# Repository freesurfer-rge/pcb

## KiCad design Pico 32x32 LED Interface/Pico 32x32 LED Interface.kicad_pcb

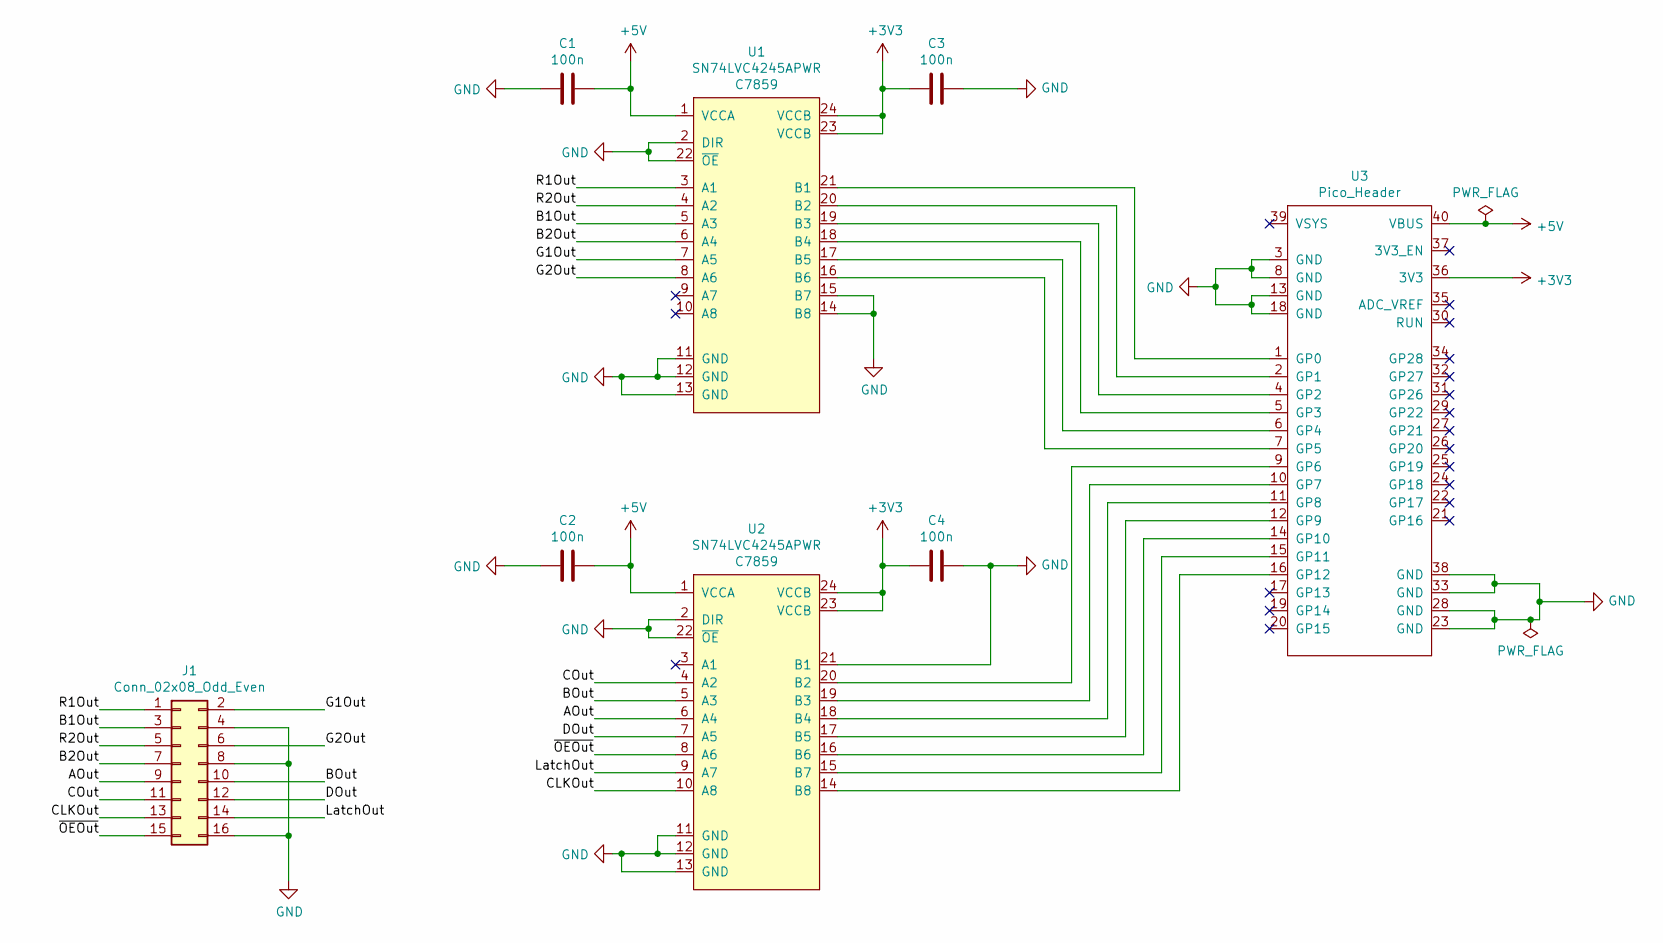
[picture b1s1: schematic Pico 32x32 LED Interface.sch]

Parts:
C1, C3: 100n; C_0402_1005Metric; LCSC C1525
C2, C4: 100n; C_0402_1005Metric_Pad0.74x0.62mm_HandSolder; LCSC C1525
J1: Conn_02x08_Odd_Even; PinHeader_2x08_P2.54mm_Vertical
U1, U2: SN74LVC4245APWR; TSSOP-24_4.4x7.8mm_P0.65mm; LCSC C7859
U3: Pico_Header; Pico_In_Headers

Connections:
+3V3: C3.2, C4.2, U1.23 (VCCB), U1.24 (VCCB), U2.23 (VCCB), U2.24 (VCCB), U3.36 (3V3)
+5V: C1.1, C2.1, U1.1 (VCCA), U2.1 (VCCA), U3.40 (VBUS)
/AOut: J1.9, U2.6 (A4)
/B1Out: J1.3, U1.5 (A3)
/B2Out: J1.7, U1.6 (A4)
/BOut: J1.10, U2.5 (A3)
/CLKOut: J1.13, U2.10 (A8)
/COut: J1.11, U2.4 (A2)
/DOut: J1.12, U2.7 (A5)
/G1Out: J1.2, U1.7 (A5)
/G2Out: J1.6, U1.8 (A6)
/LatchOut: J1.14, U2.9 (A7)
/R1Out: J1.1, U1.3 (A1)
/R2Out: J1.5, U1.4 (A2)
/~OEOut: J1.15, U2.8 (A6)
GND: C1.2, C2.2, C3.1, C4.1, J1.4, J1.8, J1.16, U1.2 (DIR), U1.11 (GND), U1.12 (GND), U1.13 (GND), U1.14 (B8), U1.15 (B7), U1.22 (~OE), U2.2 (DIR), U2.11 (GND), U2.12 (GND), U2.13 (GND), U2.21 (B1), U2.22 (~OE), U3.3 (GND), U3.8 (GND), U3.13 (GND), U3.18 (GND), U3.23 (GND), U3.28 (GND), U3.33 (GND), U3.38 (GND)
unnamed: U1.16 (B6), U3.7 (GP5)
unnamed: U1.17 (B5), U3.6 (GP4)
unnamed: U1.18 (B4), U3.5 (GP3)
unnamed: U1.19 (B3), U3.4 (GP2)
unnamed: U1.20 (B2), U3.2 (GP1)
unnamed: U1.21 (B1), U3.1 (GP0)
unnamed: U2.14 (B8), U3.16 (GP12)
unnamed: U2.15 (B7), U3.15 (GP11)
unnamed: U2.16 (B6), U3.14 (GP10)
unnamed: U2.17 (B5), U3.12 (GP9)
unnamed: U2.18 (B4), U3.11 (GP8)
unnamed: U2.19 (B3), U3.10 (GP7)
unnamed: U2.20 (B2), U3.9 (GP6)

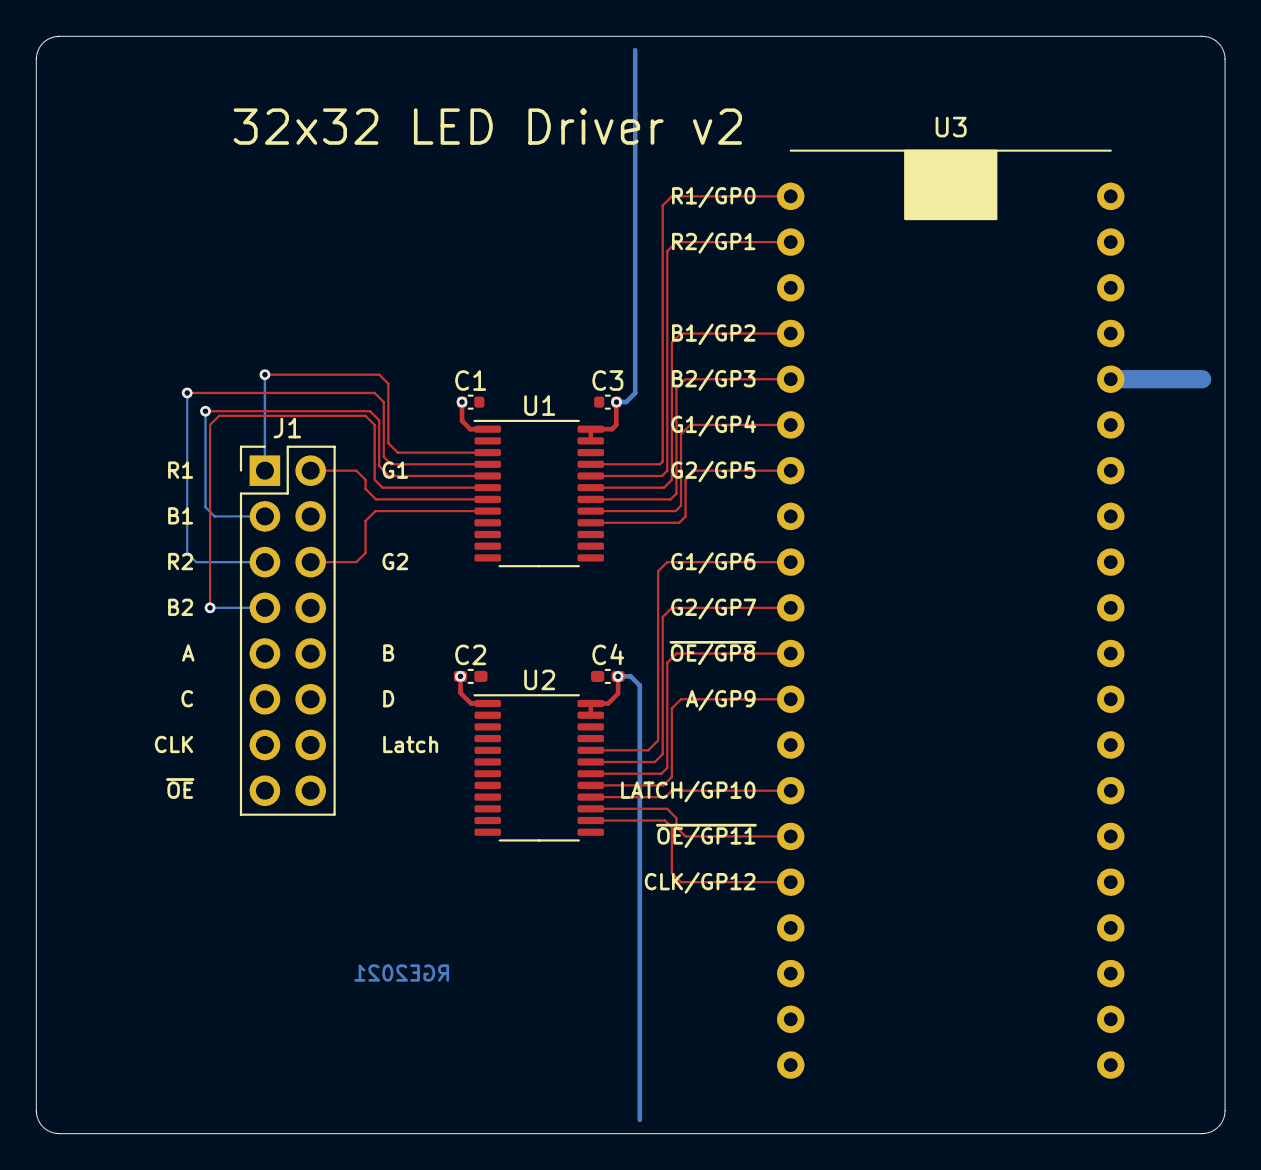
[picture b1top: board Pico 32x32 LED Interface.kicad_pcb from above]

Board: 2 copper layers, 66.0 x 61.0 mm, 8 parts (0 on the bottom side), 29 nets.

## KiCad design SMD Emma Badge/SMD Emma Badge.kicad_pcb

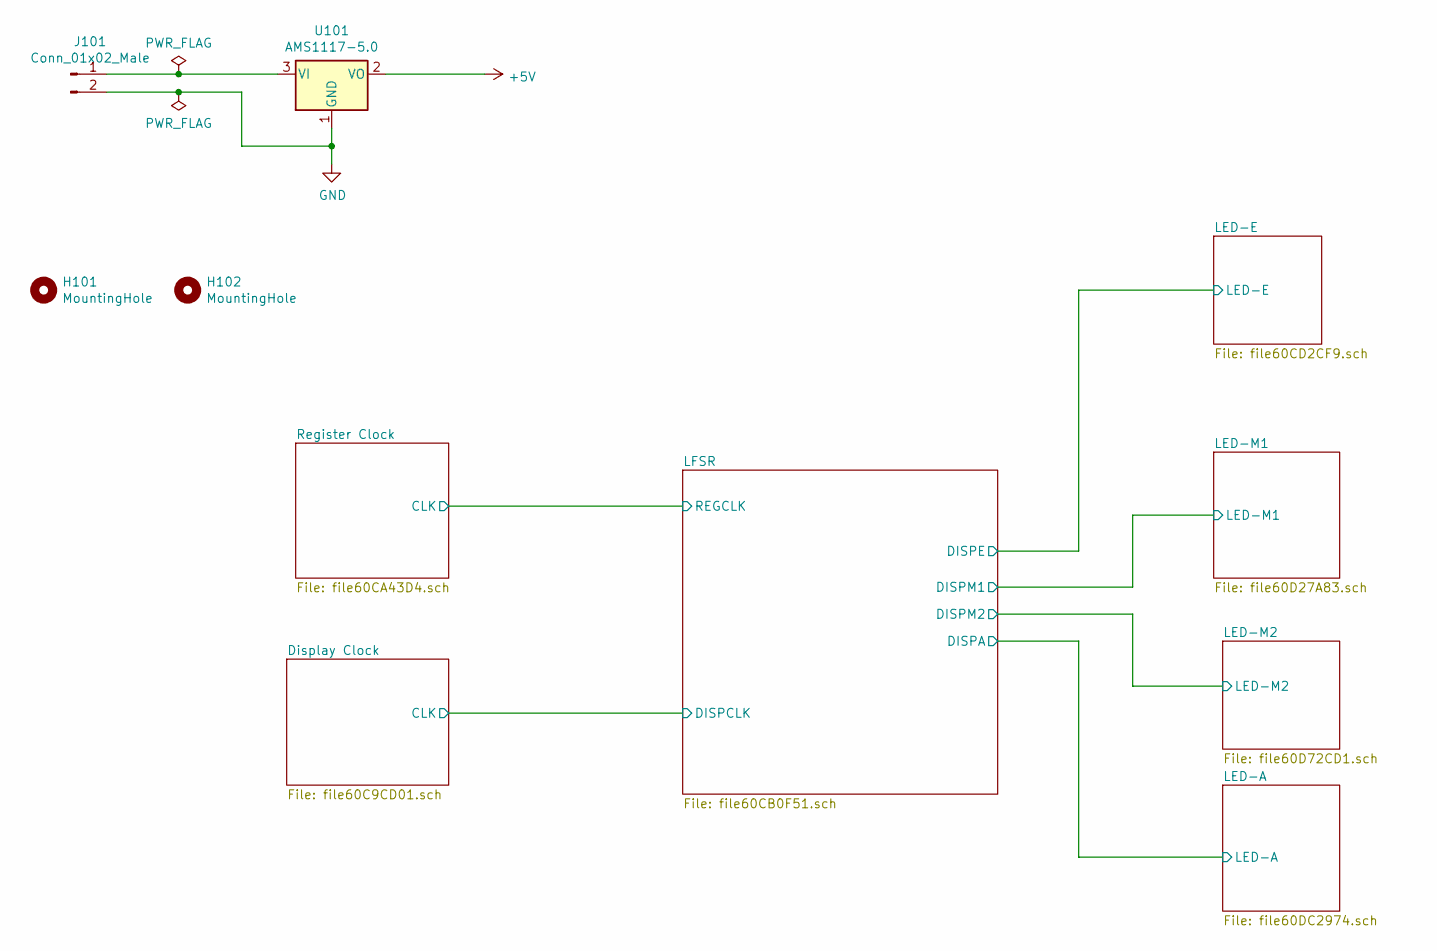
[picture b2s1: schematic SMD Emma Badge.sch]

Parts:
H101, H102: MountingHole; MountingHole_2.5mm
J101: Conn_01x02_Male; PinHeader_1x02_P2.54mm_Vertical
U101: AMS1117-5.0; SOT-223-3_TabPin2; LCSC C6187

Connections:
+5V: U101.2 (VO); also elsewhere on the board
GND: J101.2, U101.1 (GND); also elsewhere on the board
unnamed: J101.1, U101.3 (VI)

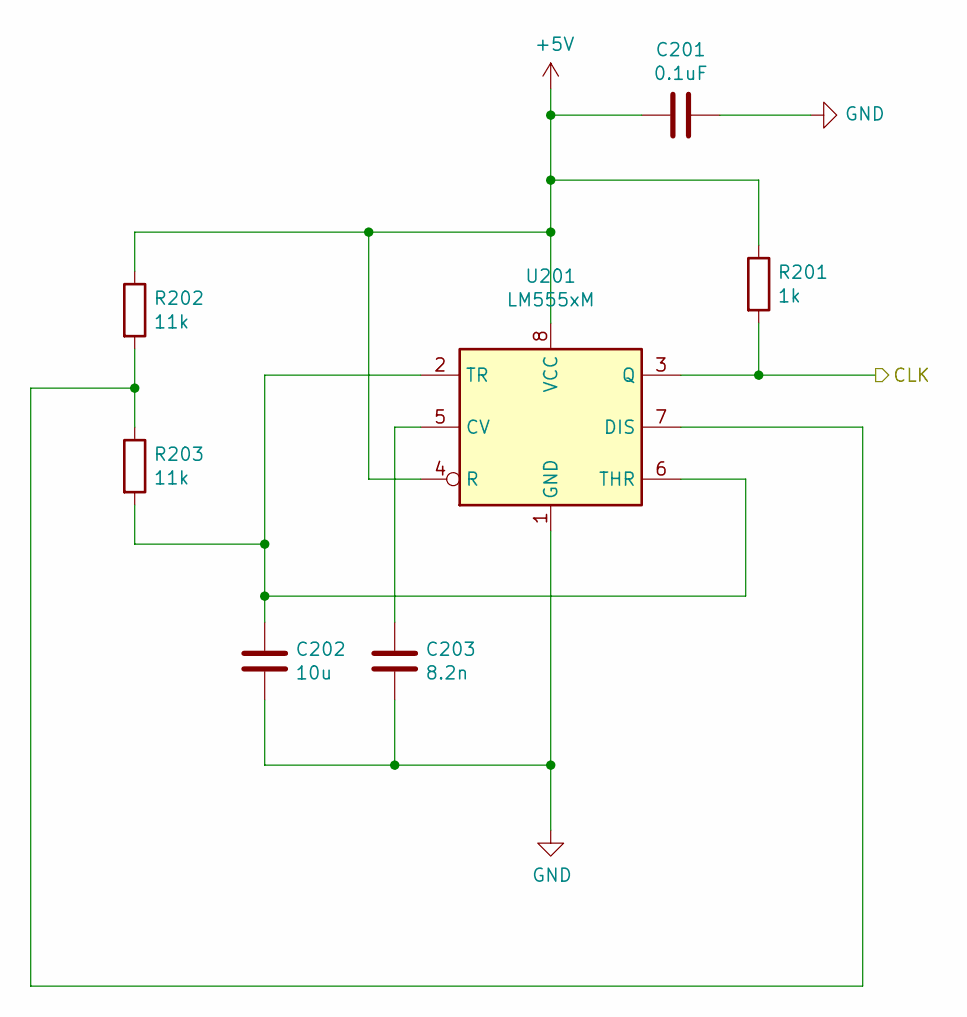
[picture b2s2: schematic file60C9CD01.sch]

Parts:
C201: 0.1uF; C_0603_1608Metric; LCSC C14663
C202: 10u; C_0603_1608Metric; LCSC C19702
C203: 8.2n; C_0603_1608Metric; LCSC C27920
R201: 1k; R_0603_1608Metric; LCSC C21190
R202, R203: 11k; R_0603_1608Metric; LCSC C25950
U201: LM555xM; SOIC-8_3.9x4.9mm_P1.27mm; LCSC C7593

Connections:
+5V: C201.2, R201.1, R202.1, U201.4 (R), U201.8 (VCC); also elsewhere on the board
/Display Clock/CLK: R201.2, U201.3 (Q); also elsewhere on the board
GND: C201.1, C202.2, C203.2, U201.1 (GND); also elsewhere on the board
unnamed: C202.1, R203.2, U201.2 (TR), U201.6 (THR)
unnamed: C203.1, U201.5 (CV)
unnamed: R202.2, R203.1, U201.7 (DIS)

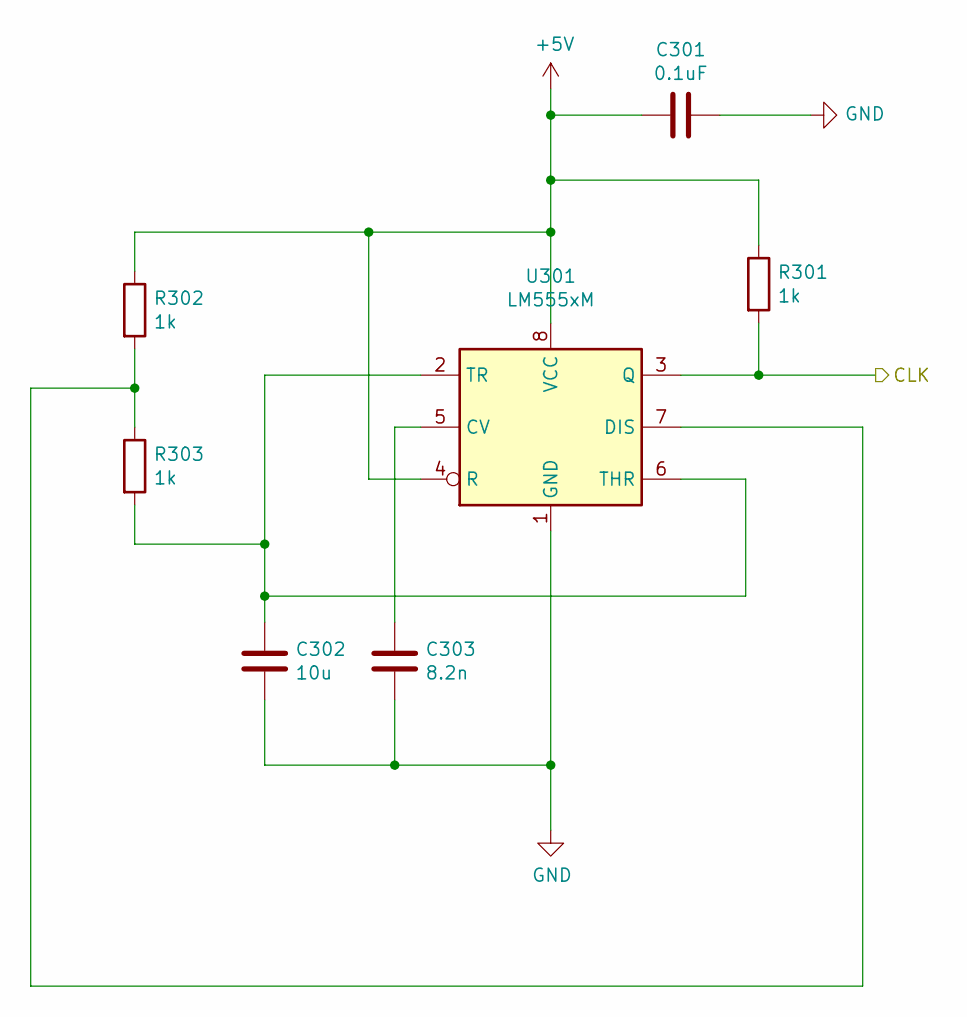
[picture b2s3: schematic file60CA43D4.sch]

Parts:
C301: 0.1uF; C_0603_1608Metric; LCSC C14663
C302: 10u; C_0603_1608Metric; LCSC C19702
C303: 8.2n; C_0603_1608Metric; LCSC C27920
R301, R302, R303: 1k; R_0603_1608Metric; LCSC C21190
U301: LM555xM; SOIC-8_3.9x4.9mm_P1.27mm; LCSC C7593

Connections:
+5V: C301.2, R301.1, R302.1, U301.4 (R), U301.8 (VCC); also elsewhere on the board
/Register Clock/CLK: R301.2, U301.3 (Q); also elsewhere on the board
GND: C301.1, C302.2, C303.2, U301.1 (GND); also elsewhere on the board
unnamed: C302.1, R303.2, U301.2 (TR), U301.6 (THR)
unnamed: C303.1, U301.5 (CV)
unnamed: R302.2, R303.1, U301.7 (DIS)

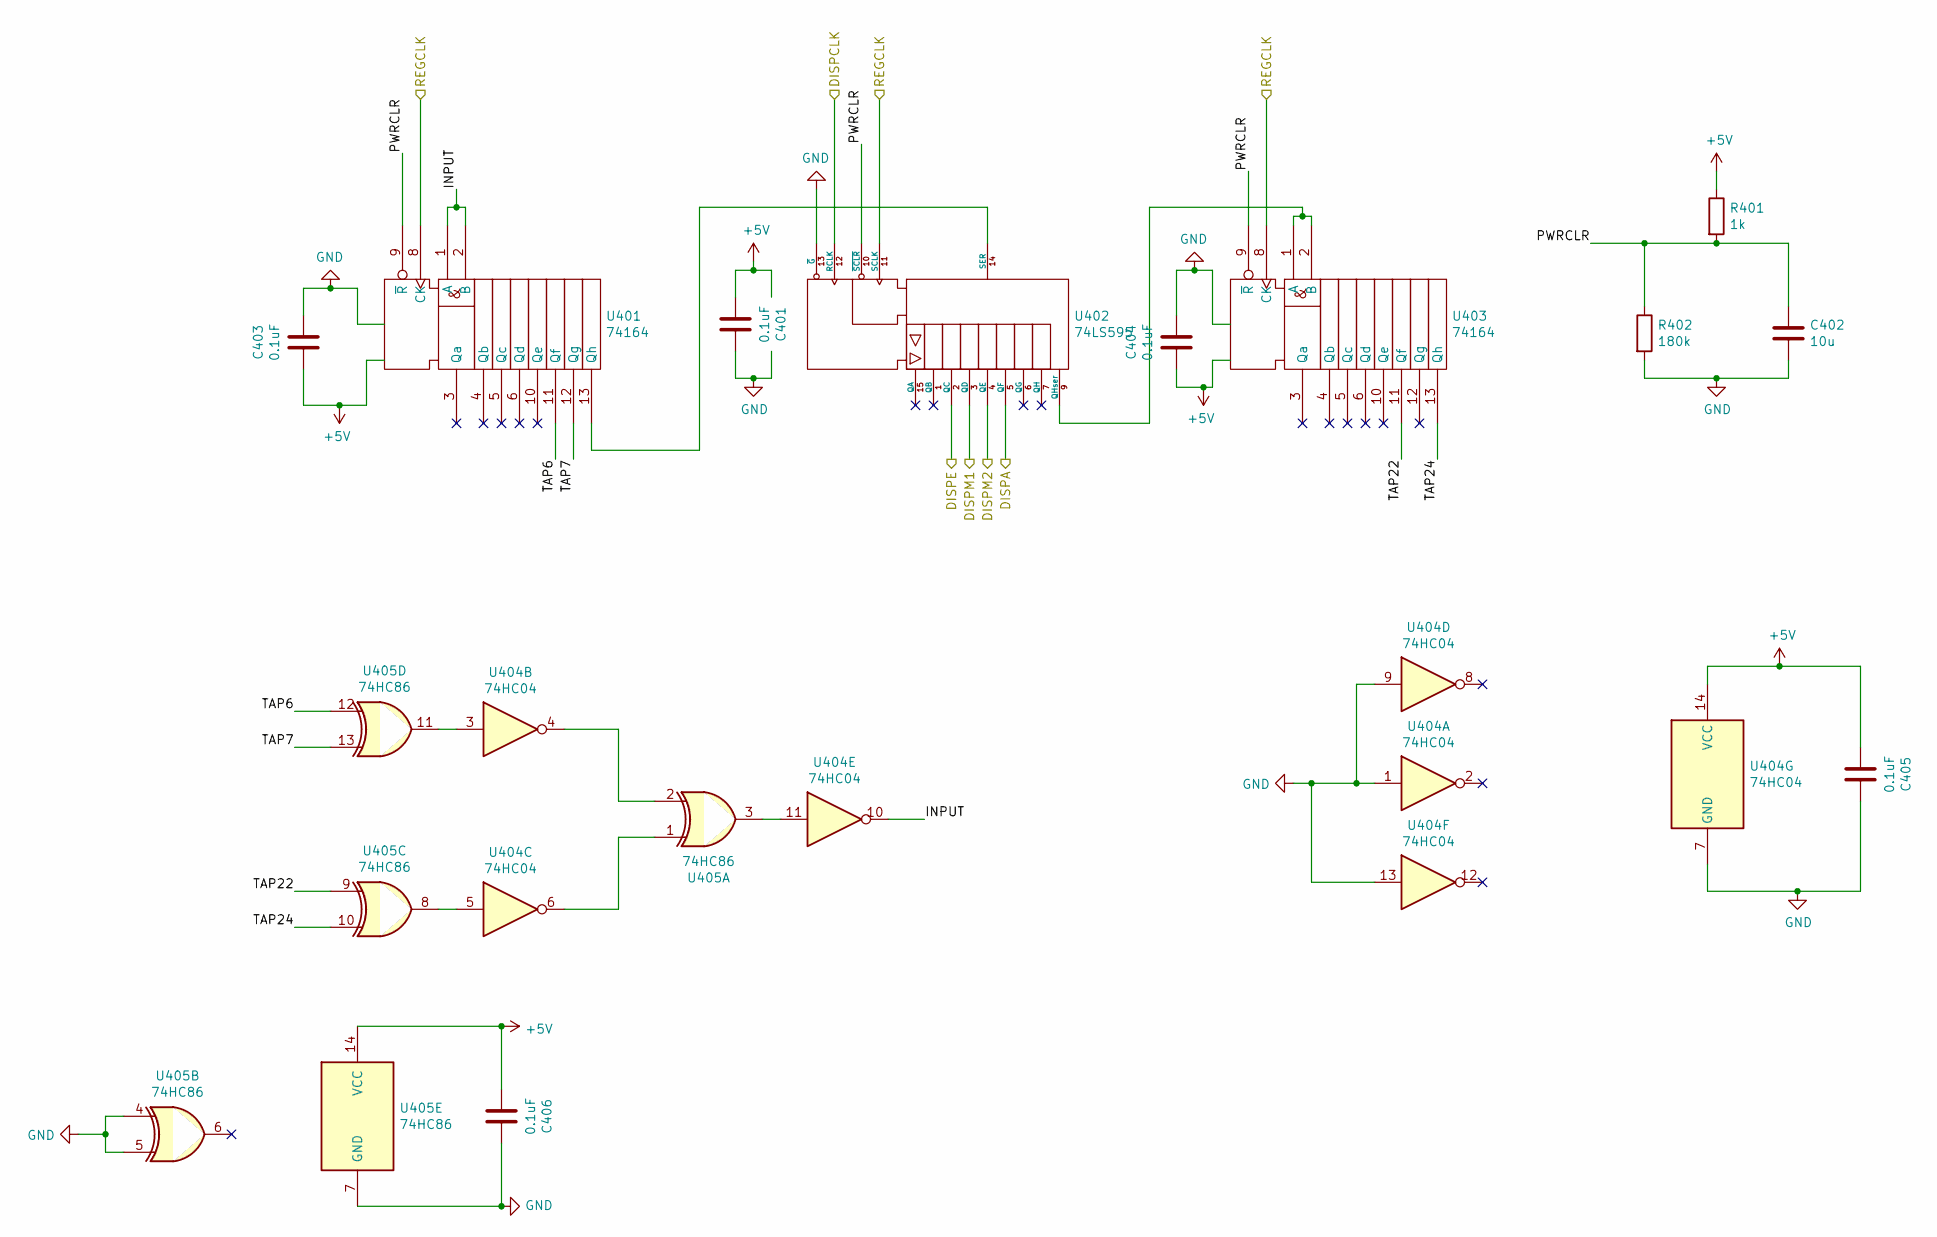
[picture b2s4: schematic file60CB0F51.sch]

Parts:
C401, C403, C404, C405, C406: 0.1uF; C_0603_1608Metric; LCSC C14663
C402: 10u; C_0603_1608Metric; LCSC C19702
R401: 1k; R_0603_1608Metric; LCSC C21190
R402: 180k; R_0603_1608Metric; LCSC C22827
U401, U403: 74164; SOIC-14_3.9x8.7mm_P1.27mm; LCSC C6825
U402: 74LS595; SOIC-16_3.9x9.9mm_P1.27mm; LCSC C5947
U404: 74HC04
U405: 74HC86

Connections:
+5V: C401.2, C403.2, C404.2, C405.2, C406.2, R401.1, U401.14 (Vdd), U402.16 (VCC), U403.14 (Vdd), U404.14 (VCC), U405.14 (VCC); also elsewhere on the board
/Display Clock/CLK: U402.12 (RCLK); also elsewhere on the board
/LFSR/DISPA: U402.5 (QF); also elsewhere on the board
/LFSR/DISPE: U402.2 (QC); also elsewhere on the board
/LFSR/DISPM1: U402.3 (QD); also elsewhere on the board
/LFSR/DISPM2: U402.4 (QE); also elsewhere on the board
/LFSR/INPUT: U401.1 (A), U401.2 (B), U404.10
/LFSR/PWRCLR: C402.1, R401.2, R402.1, U401.9 (~R), U402.10 (~SCLR), U403.9 (~R)
/LFSR/TAP6: U401.11 (Qf), U405.12
/LFSR/TAP7: U401.12 (Qg), U405.13
/LFSR/TAP22: U403.11 (Qf), U405.9
/LFSR/TAP24: U403.13 (Qh), U405.10
/Register Clock/CLK: U401.8 (CK), U402.11 (SCLK), U403.8 (CK); also elsewhere on the board
GND: C401.1, C402.2, C403.1, C404.1, C405.1, C406.1, R402.2, U401.7 (Vss), U402.8 (GND), U402.13 (~G), U403.7 (Vss), U404.1, U404.7 (GND), U404.9, U404.13, U405.4, U405.5, U405.7 (GND); also elsewhere on the board
unnamed: U401.13 (Qh), U402.14 (SER)
unnamed: U402.9 (QHser), U403.1 (A), U403.2 (B)
unnamed: U404.3, U405.11
unnamed: U404.4, U405.2
unnamed: U404.5, U405.8
unnamed: U404.6, U405.1
unnamed: U404.11, U405.3

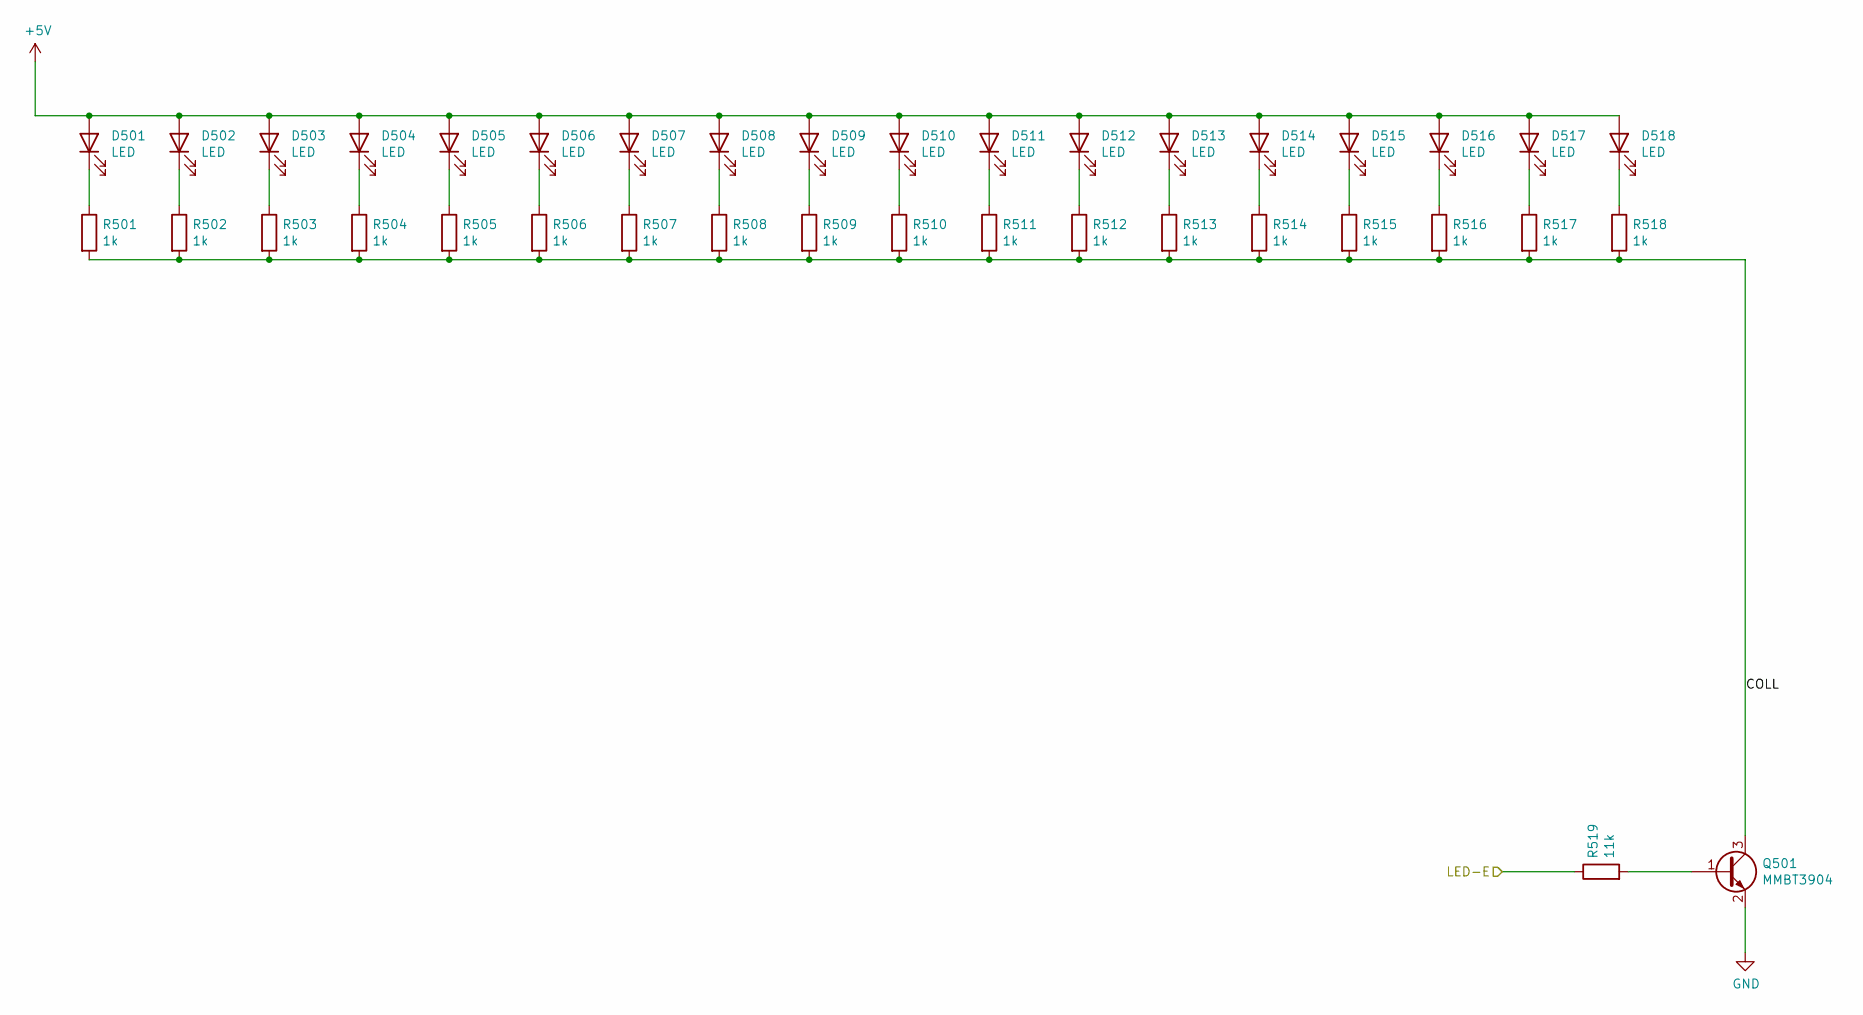
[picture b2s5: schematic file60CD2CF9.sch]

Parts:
D501, D502, D503, D504, D505, D506, D507, D508, D509, D510, D511, D512, D513, D514, D515, D516, D517, D518: LED; LED_0603_1608Metric; LCSC C2286
Q501: MMBT3904; SOT-23; LCSC C20526
R501, R502, R503, R504, R505, R506, R507, R508, R509, R510, R511, R512, R513, R514, R515, R516, R517, R518: 1k; R_0603_1608Metric; LCSC C21190
R519: 11k; R_0603_1608Metric; LCSC C25950

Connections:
+5V: D501.2 (A), D502.2 (A), D503.2 (A), D504.2 (A), D505.2 (A), D506.2 (A), D507.2 (A), D508.2 (A), D509.2 (A), D510.2 (A), D511.2 (A), D512.2 (A), D513.2 (A), D514.2 (A), D515.2 (A), D516.2 (A), D517.2 (A), D518.2 (A); also elsewhere on the board
/LED-E/COLL: Q501.3 (C), R501.2, R502.2, R503.2, R504.2, R505.2, R506.2, R507.2, R508.2, R509.2, R510.2, R511.2, R512.2, R513.2, R514.2, R515.2, R516.2, R517.2, R518.2
/LFSR/DISPE: R519.1; also elsewhere on the board
GND: Q501.2 (E); also elsewhere on the board
unnamed: D501.1 (K), R501.1
unnamed: D502.1 (K), R502.1
unnamed: D503.1 (K), R503.1
unnamed: D504.1 (K), R504.1
unnamed: D505.1 (K), R505.1
unnamed: D506.1 (K), R506.1
unnamed: D507.1 (K), R507.1
unnamed: D508.1 (K), R508.1
unnamed: D509.1 (K), R509.1
unnamed: D510.1 (K), R510.1
unnamed: D511.1 (K), R511.1
unnamed: D512.1 (K), R512.1
unnamed: D513.1 (K), R513.1
unnamed: D514.1 (K), R514.1
unnamed: D515.1 (K), R515.1
unnamed: D516.1 (K), R516.1
unnamed: D517.1 (K), R517.1
unnamed: D518.1 (K), R518.1
unnamed: Q501.1 (B), R519.2

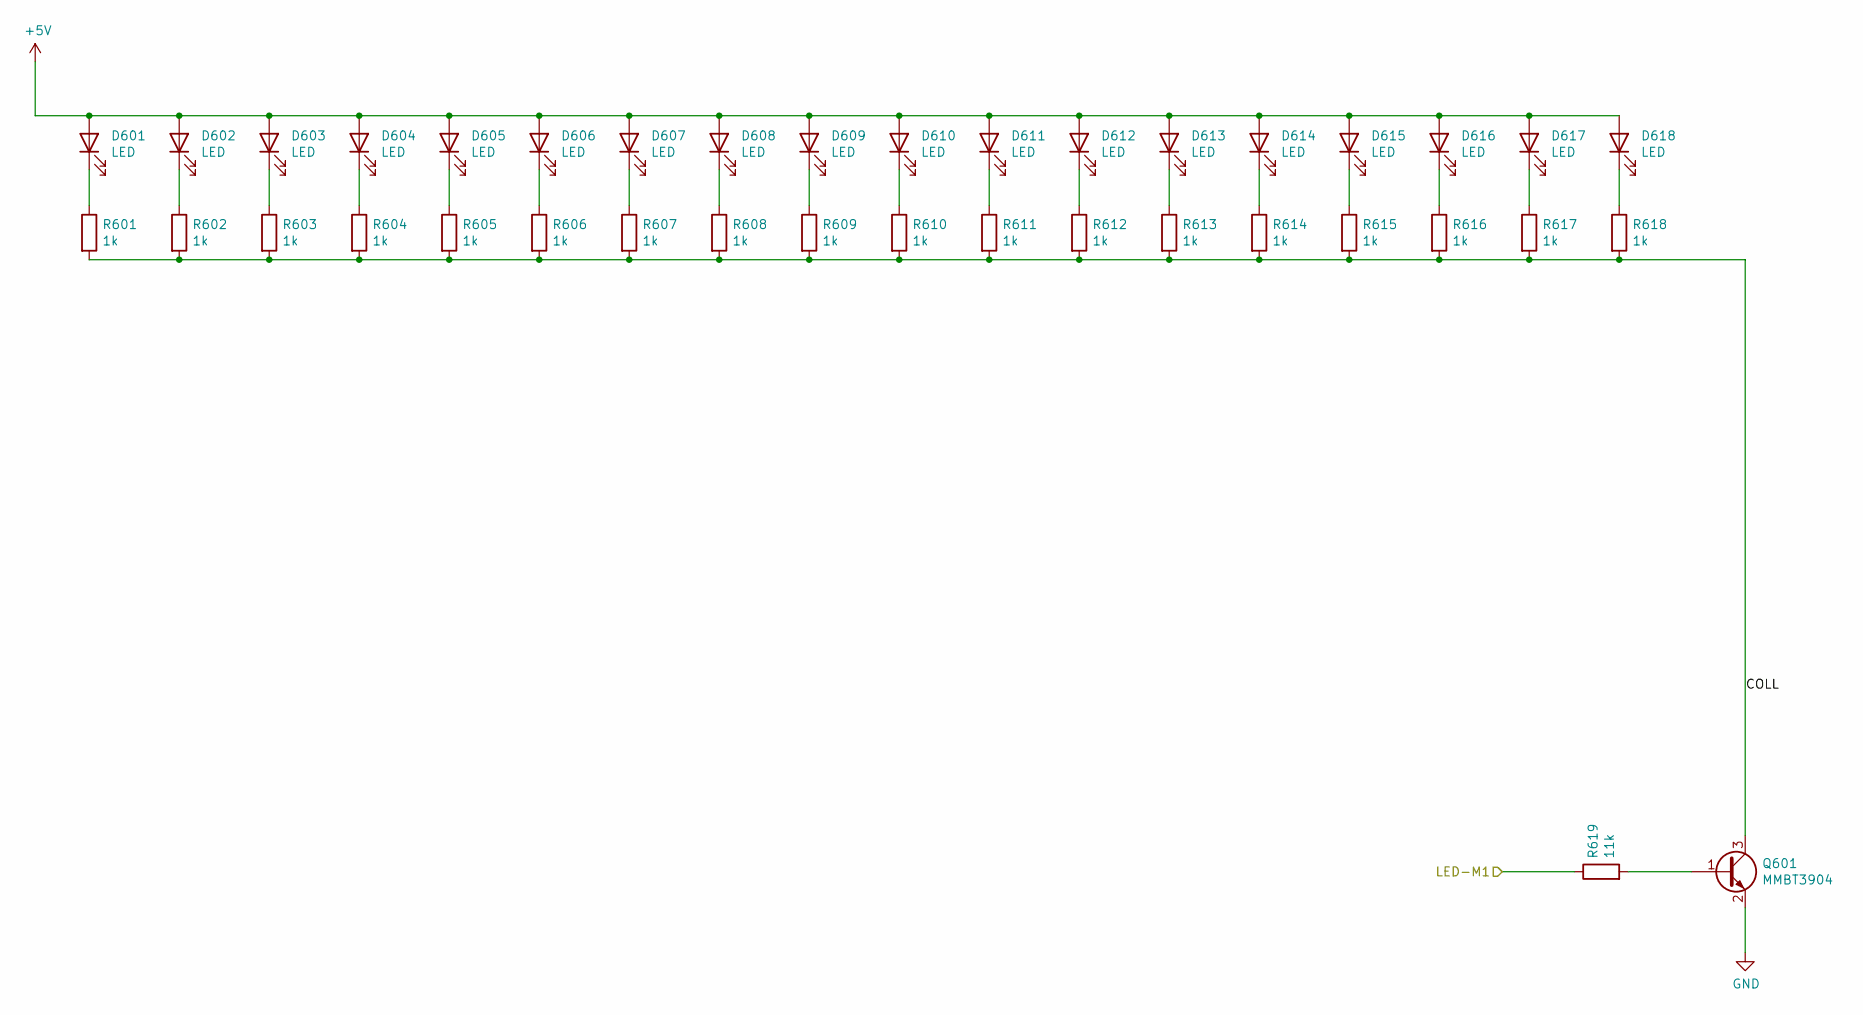
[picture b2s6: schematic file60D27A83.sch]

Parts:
D601, D602, D603, D604, D605, D606, D607, D608, D609, D610, D611, D612, D613, D614, D615, D616, D617, D618: LED; LED_0603_1608Metric; LCSC C2286
Q601: MMBT3904; SOT-23; LCSC C20526
R601, R602, R603, R604, R605, R606, R607, R608, R609, R610, R611, R612, R613, R614, R615, R616, R617, R618: 1k; R_0603_1608Metric; LCSC C21190
R619: 11k; R_0603_1608Metric; LCSC C25950

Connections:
+5V: D601.2 (A), D602.2 (A), D603.2 (A), D604.2 (A), D605.2 (A), D606.2 (A), D607.2 (A), D608.2 (A), D609.2 (A), D610.2 (A), D611.2 (A), D612.2 (A), D613.2 (A), D614.2 (A), D615.2 (A), D616.2 (A), D617.2 (A), D618.2 (A); also elsewhere on the board
/LED-M1/COLL: Q601.3 (C), R601.2, R602.2, R603.2, R604.2, R605.2, R606.2, R607.2, R608.2, R609.2, R610.2, R611.2, R612.2, R613.2, R614.2, R615.2, R616.2, R617.2, R618.2
/LFSR/DISPM1: R619.1; also elsewhere on the board
GND: Q601.2 (E); also elsewhere on the board
unnamed: D601.1 (K), R601.1
unnamed: D602.1 (K), R602.1
unnamed: D603.1 (K), R603.1
unnamed: D604.1 (K), R604.1
unnamed: D605.1 (K), R605.1
unnamed: D606.1 (K), R606.1
unnamed: D607.1 (K), R607.1
unnamed: D608.1 (K), R608.1
unnamed: D609.1 (K), R609.1
unnamed: D610.1 (K), R610.1
unnamed: D611.1 (K), R611.1
unnamed: D612.1 (K), R612.1
unnamed: D613.1 (K), R613.1
unnamed: D614.1 (K), R614.1
unnamed: D615.1 (K), R615.1
unnamed: D616.1 (K), R616.1
unnamed: D617.1 (K), R617.1
unnamed: D618.1 (K), R618.1
unnamed: Q601.1 (B), R619.2

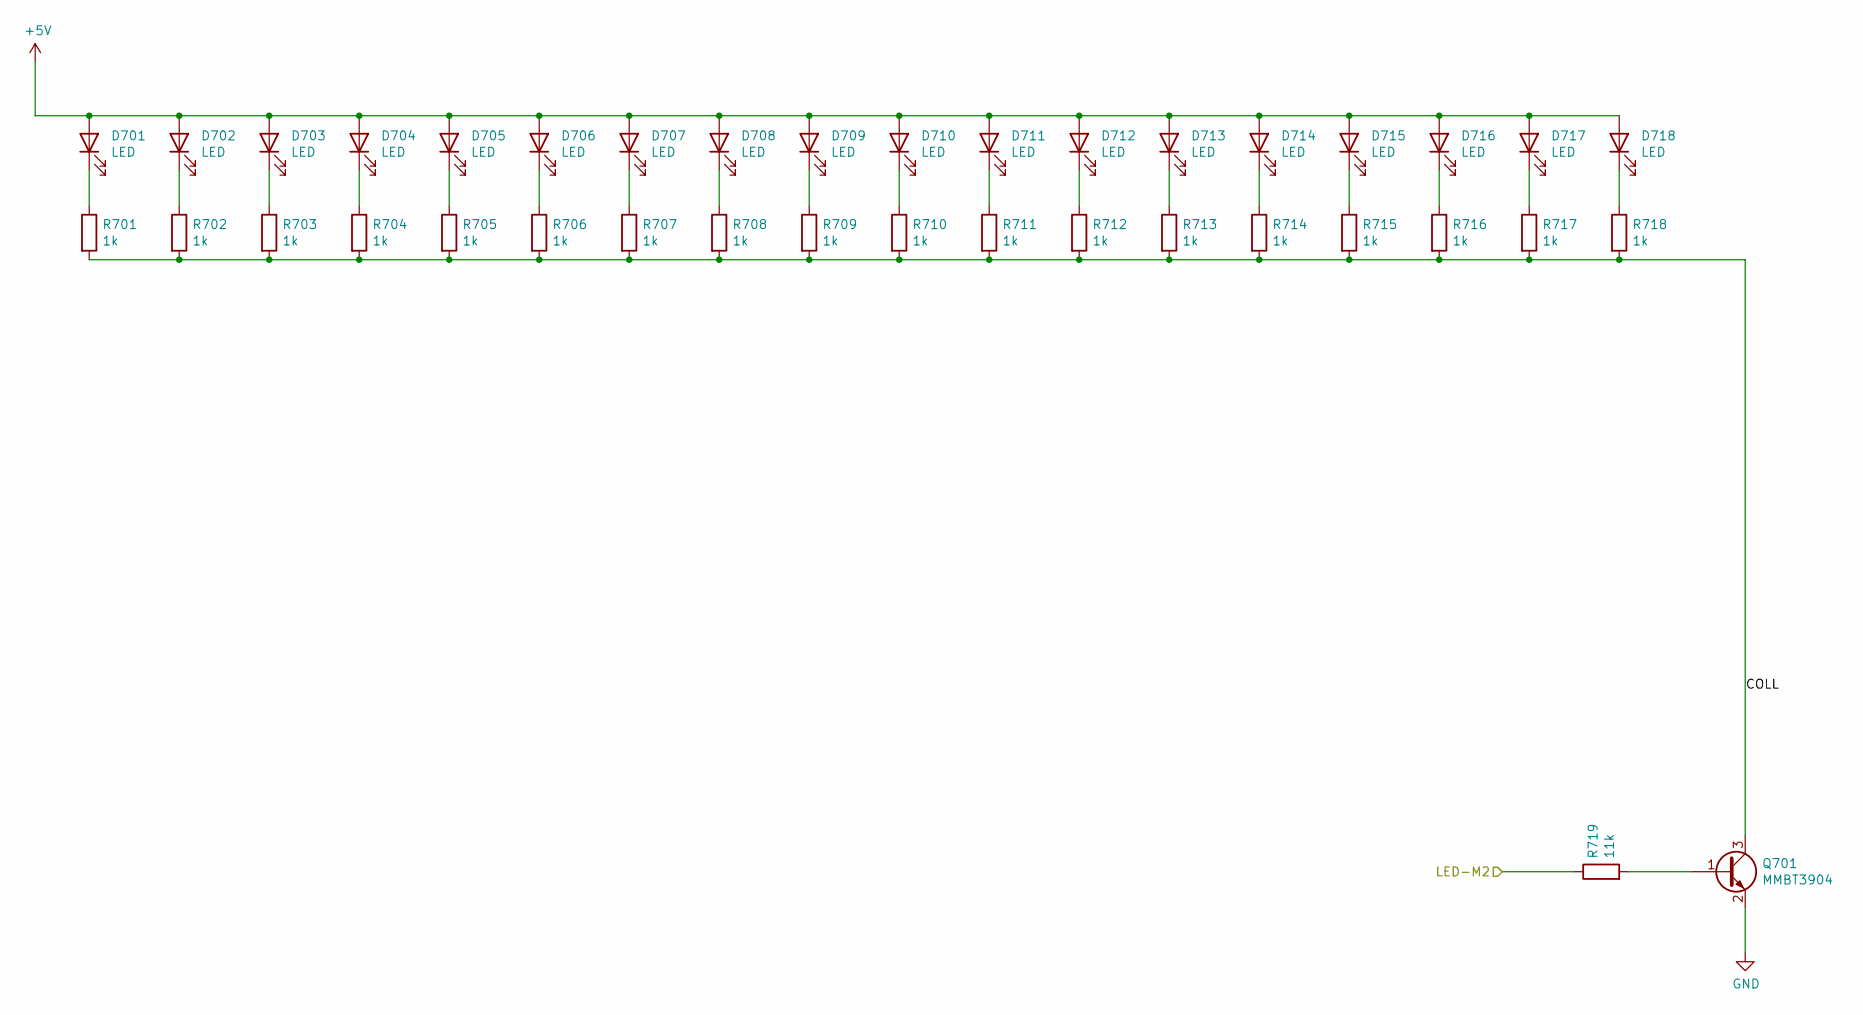
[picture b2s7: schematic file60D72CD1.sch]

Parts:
D701, D702, D703, D704, D705, D706, D707, D708, D709, D710, D711, D712, D713, D714, D715, D716, D717, D718: LED; LED_0603_1608Metric; LCSC C2286
Q701: MMBT3904; SOT-23; LCSC C20526
R701, R702, R703, R704, R705, R706, R707, R708, R709, R710, R711, R712, R713, R714, R715, R716, R717, R718: 1k; R_0603_1608Metric; LCSC C21190
R719: 11k; R_0603_1608Metric; LCSC C25950

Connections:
+5V: D701.2 (A), D702.2 (A), D703.2 (A), D704.2 (A), D705.2 (A), D706.2 (A), D707.2 (A), D708.2 (A), D709.2 (A), D710.2 (A), D711.2 (A), D712.2 (A), D713.2 (A), D714.2 (A), D715.2 (A), D716.2 (A), D717.2 (A), D718.2 (A); also elsewhere on the board
/LED-M2/COLL: Q701.3 (C), R701.2, R702.2, R703.2, R704.2, R705.2, R706.2, R707.2, R708.2, R709.2, R710.2, R711.2, R712.2, R713.2, R714.2, R715.2, R716.2, R717.2, R718.2
/LFSR/DISPM2: R719.1; also elsewhere on the board
GND: Q701.2 (E); also elsewhere on the board
unnamed: D701.1 (K), R701.1
unnamed: D702.1 (K), R702.1
unnamed: D703.1 (K), R703.1
unnamed: D704.1 (K), R704.1
unnamed: D705.1 (K), R705.1
unnamed: D706.1 (K), R706.1
unnamed: D707.1 (K), R707.1
unnamed: D708.1 (K), R708.1
unnamed: D709.1 (K), R709.1
unnamed: D710.1 (K), R710.1
unnamed: D711.1 (K), R711.1
unnamed: D712.1 (K), R712.1
unnamed: D713.1 (K), R713.1
unnamed: D714.1 (K), R714.1
unnamed: D715.1 (K), R715.1
unnamed: D716.1 (K), R716.1
unnamed: D717.1 (K), R717.1
unnamed: D718.1 (K), R718.1
unnamed: Q701.1 (B), R719.2

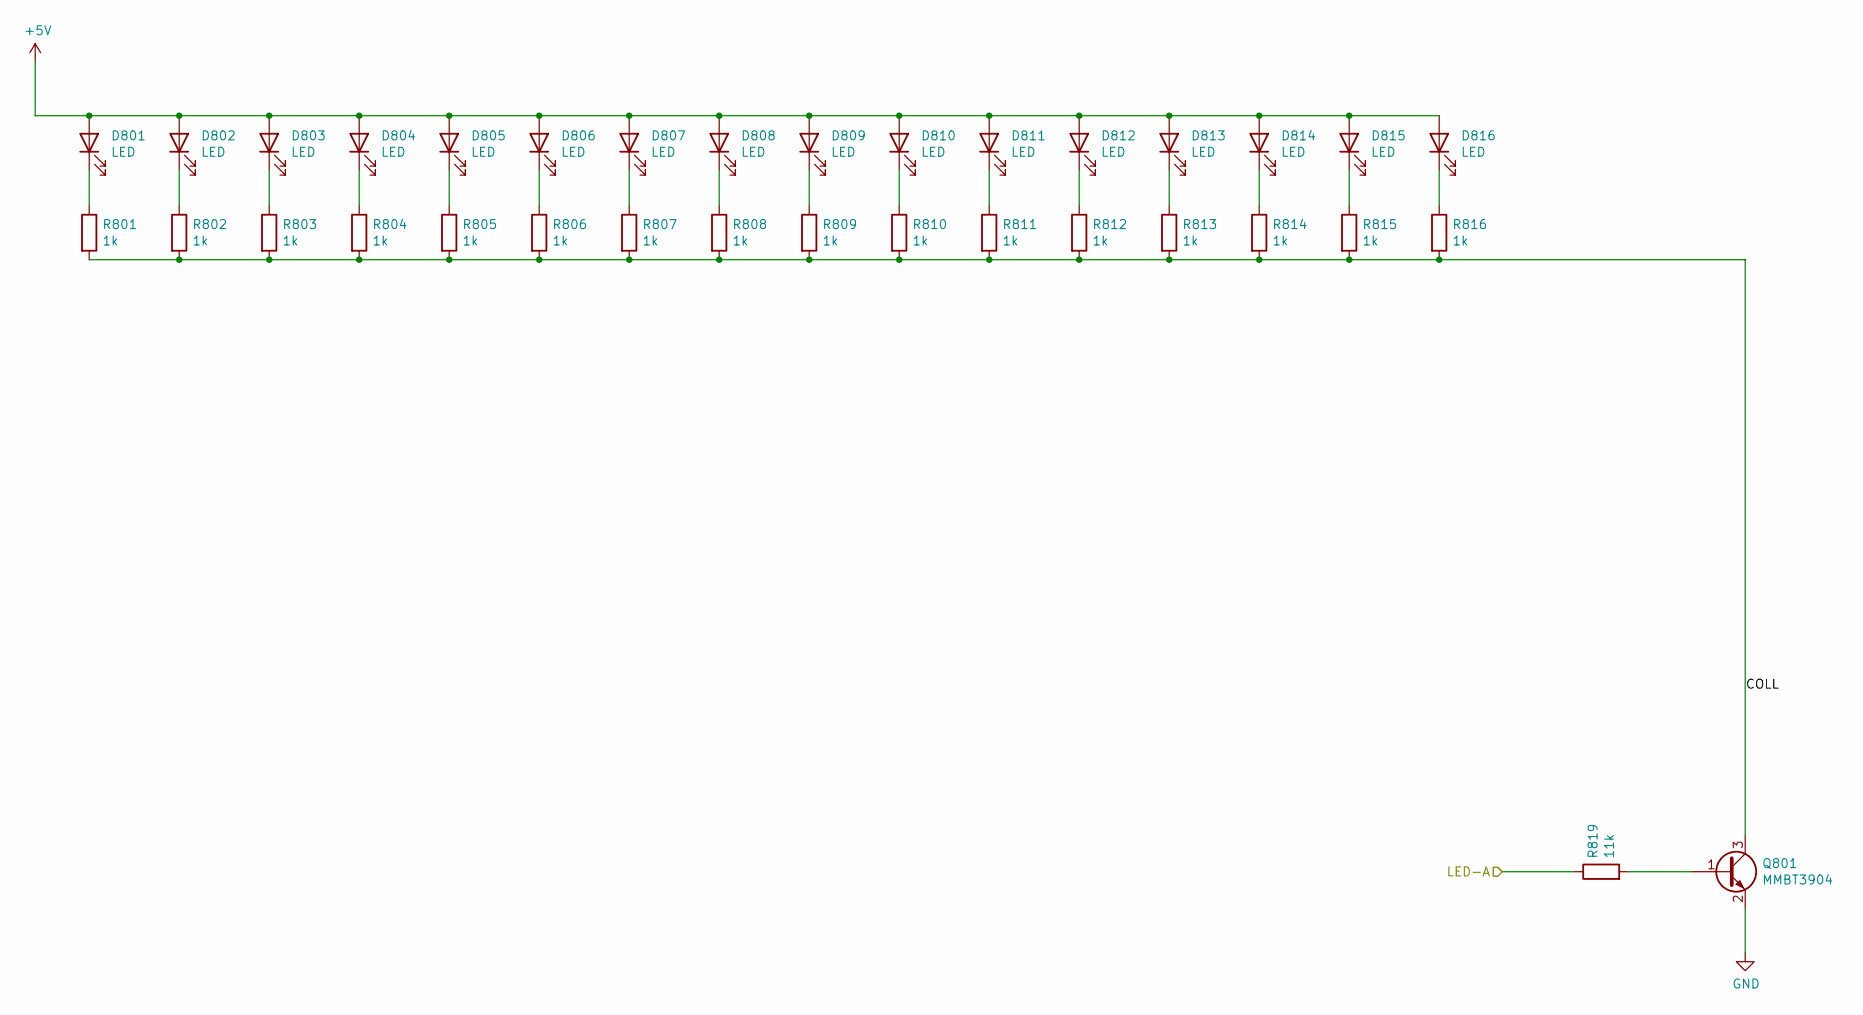
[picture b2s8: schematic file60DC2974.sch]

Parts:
D801, D802, D803, D804, D805, D806, D807, D808, D809, D810, D811, D812, D813, D814, D815, D816: LED; LED_0603_1608Metric; LCSC C2286
Q801: MMBT3904; SOT-23; LCSC C20526
R801, R802, R803, R804, R805, R806, R807, R808, R809, R810, R811, R812, R813, R814, R815, R816: 1k; R_0603_1608Metric; LCSC C21190
R819: 11k; R_0603_1608Metric; LCSC C25950

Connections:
+5V: D801.2 (A), D802.2 (A), D803.2 (A), D804.2 (A), D805.2 (A), D806.2 (A), D807.2 (A), D808.2 (A), D809.2 (A), D810.2 (A), D811.2 (A), D812.2 (A), D813.2 (A), D814.2 (A), D815.2 (A), D816.2 (A); also elsewhere on the board
/LED-A/COLL: Q801.3 (C), R801.2, R802.2, R803.2, R804.2, R805.2, R806.2, R807.2, R808.2, R809.2, R810.2, R811.2, R812.2, R813.2, R814.2, R815.2, R816.2
/LFSR/DISPA: R819.1; also elsewhere on the board
GND: Q801.2 (E); also elsewhere on the board
unnamed: D801.1 (K), R801.1
unnamed: D802.1 (K), R802.1
unnamed: D803.1 (K), R803.1
unnamed: D804.1 (K), R804.1
unnamed: D805.1 (K), R805.1
unnamed: D806.1 (K), R806.1
unnamed: D807.1 (K), R807.1
unnamed: D808.1 (K), R808.1
unnamed: D809.1 (K), R809.1
unnamed: D810.1 (K), R810.1
unnamed: D811.1 (K), R811.1
unnamed: D812.1 (K), R812.1
unnamed: D813.1 (K), R813.1
unnamed: D814.1 (K), R814.1
unnamed: D815.1 (K), R815.1
unnamed: D816.1 (K), R816.1
unnamed: Q801.1 (B), R819.2
